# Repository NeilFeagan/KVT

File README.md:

# KVT
Open source southpaw mechanical keyboard. This Github comes with both the project files and libraries used on the project.
Note I do not own the libraries used, I have only modified them to fit my needs.

## Features
* USB Type-C
* Southpaw Layout
* All Through Hole Components
* LED Support
* QMK

## Bill Of Materials
* Proton_C: 1
* KVT PCB: 1
* MX Style Switches: 104
* 1N4148 Through Hole Diodes: 104
* JS202011AQN DPDT Switch: 1 (Right Angle)
* 470Ω resistors: 104
* LEDs: 104

## Installing and Compiling
To install QMK visit QMK's official website https://docs.qmk.fm/#/

**You will need all the sub-modules to compile the firmware**

After installation you need to compile the firmware; To compile the firmware for the Proton_C type this into the terminal

```
 make kv\revt:default
```
## Keymaps
Default Keymap

FN Layer Keymap

## Warning
This keyboard does not include a backplate or case, you will have to make your own.

KiCad 5.1.2 or above is needed to open this project. KiCad 4 or below won't work.

## Notes
I made this keyboard for a personal project, I am new to the circuit/keyboard designing in game. If you open the pcb design you will see a bunch of numbers to the left of the finished design, those are spacing numbers for the footprints that I used.   

If you have any suggestions on improving the design message me on Reddit /u/Hybrid65, thank you.

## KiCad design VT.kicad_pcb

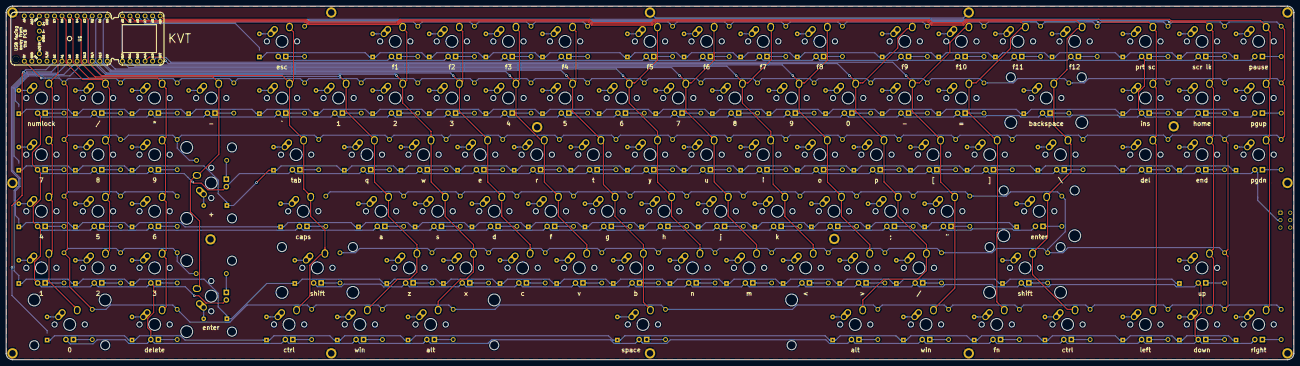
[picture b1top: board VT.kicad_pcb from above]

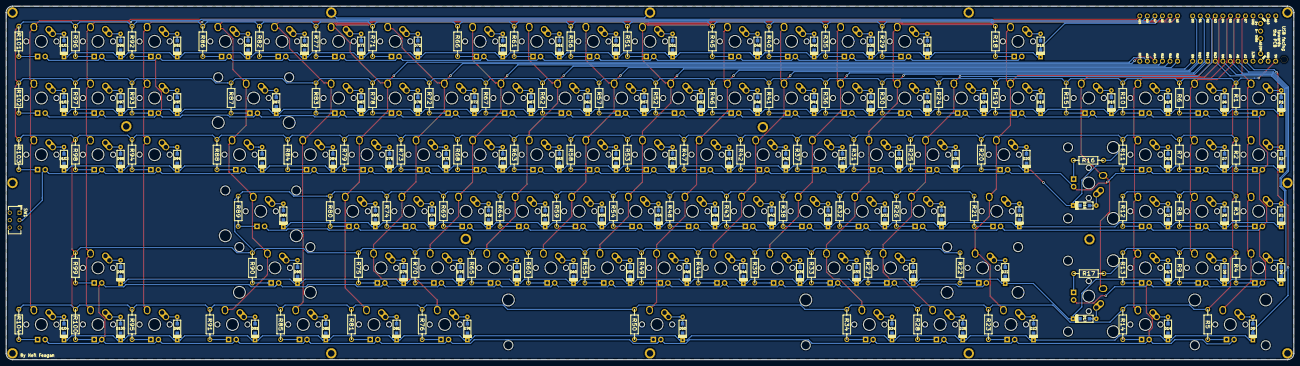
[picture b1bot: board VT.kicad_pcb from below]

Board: 2 copper layers, 433.3 x 119.0 mm, 434 parts (210 on the bottom side), 238 nets.

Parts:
D1, D2, D3, D4, D5, D6, D7, D8, D9, D10, D11, D12, D13, D14, D15, D16, D17, D18, D19, D20, D21, D22, D23, D24, D25, D26, D27, D28, D29, D30, D31, D32, D33, D34, D35, D36, D37, D38, D39, D40, D41, D42, D43, D44, D45, D46, D47, D48, D49, D50, D51, D52, D53, D54, D55, D56, D57, D58, D59, D60, D61, D62, D63, D64, D65, D66, D67, D68, D69, D70, D71, D72, D73, D74, D75, D76, D77, D78, D79, D80, D81, D82, D83, D84, D85, D86, D87, D88, D89, D90, D91, D92, D93, D94, D95, D96, D97, D98, D99, D100, D101, D102, D103, D104: D; D_SOD123_axial
D105, D106, D107, D108, D109, D110, D111, D112, D113, D114, D115, D116, D117, D118, D119, D120, D121, D122, D123, D124, D125, D126, D127, D128, D129, D130, D131, D132, D133, D134, D135, D136, D137, D138, D139, D140, D141, D142, D143, D144, D145, D146, D147, D148, D149, D150, D151, D152, D153, D154, D155, D156, D157, D158, D159, D160, D161, D162, D163, D164, D165, D166, D167, D168, D169, D170, D171, D172, D173, D174, D175, D176, D177, D178, D179, D180, D181, D182, D183, D184, D185, D186, D187, D188, D189, D190, D191, D192, D193, D194, D195, D196, D197, D198, D199, D200, D201, D202, D203, D204, D205, D206, D207, D208: LED; LED_E
H1, H2, H3, H4, H5, H6, H7, H8, H9, H10, H11, H12, H13, H14, H15, H16: MH_Pad; MountingHole_2.2mm_M2_ISO7380_Pad
K1, K2, K3, K4, K6, K7, K8, K9, K10, K11, K12, K13, K14, K15, K18, K19, K24, K25, K26, K27, K29, K30, K31, K32, K33, K35, K36, K37, K38, K39, K40, K41, K42, K43, K44, K45, K46, K47, K48, K49, K51, K52, K53, K54, K55, K56, K57, K58, K59, K60, K61, K62, K63, K64, K65, K66, K67, K68, K69, K70, K71, K72, K73, K74, K75, K77, K78, K79, K80, K82, K83, K84, K86, K92, K93, K94, K95, K96, K97, K98, K99, K100, K101, K102, K103, K104: KEYSW; MX-1U-NoLED_E
K5, K16, K17: KEYSW; MX-2U-ReversedStabilizers-NoLED_E
K20, K88: KEYSW; MX-1.5U-NoLED_E
K21: KEYSW; MX-1.75U-NoLED_E
K22, K89: KEYSW; MX-2.25U-NoLED_E
K23, K28, K34, K76, K81, K85, K91: KEYSW; MX-1.25U-NoLED_E
K50: KEYSW; MX-6.25U-ReversedStabilizers-NoLED_E
K87: KEYSW; MX-2U-NoLED_E
K90: KEYSW; MX-2.75U-NoLED_E
R1, R2, R3, R4, R5, R6, R7, R8, R9, R10, R11, R12, R13, R14, R15, R16, R17, R18, R19, R20, R21, R22, R23, R24, R25, R26, R27, R28, R29, R30, R31, R32, R33, R34, R35, R36, R37, R38, R39, R40, R41, R42, R43, R44, R45, R46, R47, R48, R49, R50, R51, R52, R53, R54, R55, R56, R57, R58, R59, R60, R61, R62, R63, R64, R65, R66, R67, R68, R69, R70, R71, R72, R73, R74, R75, R76, R77, R78, R79, R80, R81, R82, R83, R84, R85, R86, R87, R88, R89, R90, R91, R92, R93, R94, R95, R96, R97, R98, R99, R100, R101, R102, R103, R104: 470; RESISTOR
SW1: SW_SPST; SW_CuK_JS202011AQN_DPDT_Angled
U1: proton_c; proton_c_E

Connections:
/col0: K1.1, K2.1, K3.1, K4.1, K5.1, U1.B7
/col1: K6.1, K7.1, K8.1, K9.1, U1.B6
/col2: K10.1, K11.1, K12.1, K13.1, K14.1, U1.B5
/col3: K15.1, K16.1, K17.1, U1.B4
/col4: K18.1, K19.1, K20.1, K21.1, K22.1, K23.1, U1.B3
/col5: K24.1, K25.1, K26.1, K27.1, K28.1, U1.B2
/col6: K29.1, K30.1, K31.1, K32.1, K33.1, K34.1, U1.B14
/col7: K35.1, K36.1, K37.1, K38.1, K39.1, U1.B1
/col8: K40.1, K41.1, K42.1, K43.1, K44.1, U1.B15
/col9: K45.1, K46.1, K47.1, K48.1, K49.1, K50.1, U1.B0
/col10: K51.1, K52.1, K53.1, K54.1, K55.1, U1.B9
/col11: K56.1, K57.1, K58.1, K59.1, K60.1, U1.B10
/col12: K61.1, K62.1, K63.1, K64.1, K65.1, U1.B11
/col13: K66.1, K67.1, K68.1, K69.1, K70.1, U1.B12
/col14: K71.1, K72.1, K73.1, K74.1, K75.1, K76.1, U1.A14
/col15: K77.1, K78.1, K79.1, K80.1, K81.1, U1.A13
/col16: K82.1, K83.1, K84.1, K85.1, U1.A4
/col17: K86.1, K87.1, K88.1, K89.1, K90.1, K91.1, U1.A5
/col18: K92.1, K93.1, K94.1, K95.1, U1.A7
/col19: K96.1, K97.1, K98.1, K99.1, K100.1, U1.A8
/col20: K101.1, K102.1, K103.1, K104.1, U1.A15
/row0: D18.1, D29.1, D35.1, D40.1, D45.1, D51.1, D56.1, D61.1, D66.1, D71.1, D77.1, D82.1, D86.1, D92.1, D96.1, D101.1, U1.A6
/row1: D1.1, D6.1, D10.1, D15.1, D19.1, D24.1, D30.1, D36.1, D41.1, D46.1, D52.1, D57.1, D62.1, D67.1, D72.1, D78.1, D83.1, D87.1, D93.1, D97.1, D102.1, U1.B13
/row2: D2.1, D7.1, D11.1, D16.1, D20.1, D25.1, D31.1, D37.1, D42.1, D47.1, D53.1, D58.1, D63.1, D68.1, D73.1, D79.1, D84.1, D88.1, D94.1, D98.1, D103.1, U1.B8
/row3: D3.1, D8.1, D12.1, D21.1, D26.1, D32.1, D38.1, D43.1, D48.1, D54.1, D59.1, D64.1, D69.1, D74.1, D80.1, D89.1, U1.A0
/row4: D4.1, D9.1, D13.1, D17.1, D22.1, D27.1, D33.1, D39.1, D44.1, D49.1, D55.1, D60.1, D65.1, D70.1, D75.1, D90.1, D99.1, U1.A1
/row5: D5.1, D14.1, D23.1, D28.1, D34.1, D50.1, D76.1, D81.1, D85.1, D91.1, D95.1, D100.1, D104.1, U1.A2
GND: H1.1, H2.1, H3.1, H4.1, H5.1, H6.1, H7.1, H8.1, H9.1, H10.1, H11.1, H12.1, H13.1, H14.1, H15.1, H16.1, SW1.1, U1.GND
unnamed: D1.2, K1.2
unnamed: D2.2, K2.2
unnamed: D3.2, K3.2
unnamed: D4.2, K4.2
unnamed: D5.2, K5.2
unnamed: D6.2, K6.2
unnamed: D7.2, K7.2
unnamed: D8.2, K8.2
unnamed: D9.2, K9.2
unnamed: D10.2, K10.2
unnamed: D11.2, K11.2
unnamed: D12.2, K12.2
unnamed: D13.2, K13.2
unnamed: D14.2, K14.2
unnamed: D15.2, K15.2
unnamed: D16.2, K16.2
unnamed: D17.2, K17.2
unnamed: D18.2, K18.2
unnamed: D19.2, K19.2
unnamed: D20.2, K20.2
unnamed: D21.2, K21.2
unnamed: D22.2, K22.2
unnamed: D23.2, K23.2
unnamed: D24.2, K24.2
unnamed: D25.2, K25.2
unnamed: D26.2, K26.2
unnamed: D27.2, K27.2
unnamed: D28.2, K28.2
unnamed: D29.2, K29.2
unnamed: D30.2, K30.2
unnamed: D31.2, K31.2
unnamed: D32.2, K32.2
unnamed: D33.2, K33.2
unnamed: D34.2, K34.2
unnamed: D35.2, K35.2
unnamed: D36.2, K36.2
unnamed: D37.2, K37.2
unnamed: D38.2, K38.2
unnamed: D39.2, K39.2
unnamed: D40.2, K40.2
unnamed: D41.2, K41.2
unnamed: D42.2, K42.2
unnamed: D43.2, K43.2
unnamed: D44.2, K44.2
unnamed: D45.2, K45.2
unnamed: D46.2, K46.2
unnamed: D47.2, K47.2
unnamed: D48.2, K48.2
unnamed: D49.2, K49.2
unnamed: D50.2, K50.2
unnamed: D51.2, K51.2
unnamed: D52.2, K52.2
unnamed: D53.2, K53.2
unnamed: D54.2, K54.2
unnamed: D55.2, K55.2
unnamed: D56.2, K56.2
unnamed: D57.2, K57.2
unnamed: D58.2, K58.2
unnamed: D59.2, K59.2
unnamed: D60.2, K60.2
unnamed: D61.2, K61.2
unnamed: D62.2, K62.2
unnamed: D63.2, K63.2
unnamed: D64.2, K64.2
unnamed: D65.2, K65.2
unnamed: D66.2, K66.2
unnamed: D67.2, K67.2
unnamed: D68.2, K68.2
unnamed: D69.2, K69.2
unnamed: D70.2, K70.2
unnamed: D71.2, K71.2
unnamed: D72.2, K72.2
unnamed: D73.2, K73.2
unnamed: D74.2, K74.2
unnamed: D75.2, K75.2
unnamed: D76.2, K76.2
unnamed: D77.2, K77.2
unnamed: D78.2, K78.2
unnamed: D79.2, K79.2
unnamed: D80.2, K80.2
unnamed: D81.2, K81.2
unnamed: D82.2, K82.2
unnamed: D83.2, K83.2
unnamed: D84.2, K84.2
unnamed: D85.2, K85.2
unnamed: D86.2, K86.2
unnamed: D87.2, K87.2
unnamed: D88.2, K88.2
unnamed: D89.2, K89.2
unnamed: D90.2, K90.2
unnamed: D91.2, K91.2
unnamed: D92.2, K92.2
unnamed: D93.2, K93.2
unnamed: D94.2, K94.2
unnamed: D95.2, K95.2
unnamed: D96.2, K96.2
unnamed: D97.2, K97.2
unnamed: D98.2, K98.2
unnamed: D99.2, K99.2
unnamed: D100.2, K100.2
unnamed: D101.2, K101.2
unnamed: D102.2, K102.2
unnamed: D103.2, K103.2
unnamed: D104.2, K104.2
unnamed: D105.1, D106.1, D107.1, D108.1, D109.1, D110.1, D111.1, D112.1, D113.1, D114.1, D115.1, D116.1, D117.1, D118.1, D119.1, D120.1, D121.1, D122.1, D123.1, D124.1, D125.1, D126.1, D127.1, D128.1, D129.1, D130.1, D131.1, D132.1, D133.1, D134.1, D135.1, D136.1, D137.1, D138.1, D139.1, D140.1, D141.1, D142.1, D143.1, D144.1, D145.1, D146.1, D147.1, D148.1, D149.1, D150.1, D151.1, D152.1, D153.1, D154.1, D155.1, D156.1, D157.1, D158.1, D159.1, D160.1, D161.1, D162.1, D163.1, D164.1, D165.1, D166.1, D167.1, D168.1, D169.1, D170.1, D171.1, D172.1, D173.1, D174.1, D175.1, D176.1, D177.1, D178.1, D179.1, D180.1, D181.1, D182.1, D183.1, D184.1, D185.1, D186.1, D187.1, D188.1, D189.1, D190.1, D191.1, D192.1, D193.1, D194.1, D195.1, D196.1, D197.1, D198.1, D199.1, D200.1, D201.1, D202.1, D203.1, D204.1, D205.1, D206.1, D207.1, D208.1, SW1.2
unnamed: D105.2, R1.2
unnamed: D106.2, R2.2
unnamed: D107.2, R3.2
unnamed: D108.2, R4.2
unnamed: D109.2, R5.2
unnamed: D110.2, R6.2
unnamed: D111.2, R7.2
unnamed: D112.2, R8.2
unnamed: D113.2, R9.2
unnamed: D114.2, R10.2
unnamed: D115.2, R11.2
unnamed: D116.2, R12.2
unnamed: D117.2, R13.2
unnamed: D118.2, R14.2
unnamed: D119.2, R15.2
unnamed: D120.2, R16.2
unnamed: D121.2, R17.2
unnamed: D122.2, R18.2
unnamed: D123.2, R19.2
unnamed: D124.2, R20.2
unnamed: D125.2, R21.2
unnamed: D126.2, R22.2
unnamed: D127.2, R23.2
unnamed: D128.2, R24.2
unnamed: D129.2, R25.2
unnamed: D130.2, R26.2
unnamed: D131.2, R27.2
unnamed: D132.2, R28.2
unnamed: D133.2, R29.2
unnamed: D134.2, R30.2
unnamed: D135.2, R31.2
unnamed: D136.2, R32.2
unnamed: D137.2, R33.2
unnamed: D138.2, R34.2
unnamed: D139.2, R35.2
unnamed: D140.2, R36.2
unnamed: D141.2, R37.2
unnamed: D142.2, R38.2
unnamed: D143.2, R39.2
unnamed: D144.2, R40.2
unnamed: D145.2, R41.2
unnamed: D146.2, R42.2
unnamed: D147.2, R43.2
unnamed: D148.2, R44.2
unnamed: D149.2, R45.2
unnamed: D150.2, R46.2
unnamed: D151.2, R47.2
unnamed: D152.2, R48.2
unnamed: D153.2, R49.2
unnamed: D154.2, R50.2
unnamed: D155.2, R51.2
unnamed: D156.2, R52.2
unnamed: D157.2, R53.2
unnamed: D158.2, R54.2
unnamed: D159.2, R55.2
unnamed: D160.2, R56.2
unnamed: D161.2, R57.2
unnamed: D162.2, R58.2
unnamed: D163.2, R59.2
unnamed: D164.2, R60.2
unnamed: D165.2, R61.2
unnamed: D166.2, R62.2
unnamed: D167.2, R63.2
unnamed: D168.2, R64.2
unnamed: D169.2, R65.2
unnamed: D170.2, R66.2
unnamed: D171.2, R67.2
unnamed: D172.2, R68.2
unnamed: D173.2, R69.2
unnamed: D174.2, R70.2
unnamed: D175.2, R71.2
unnamed: D176.2, R72.2
unnamed: D177.2, R73.2
unnamed: D178.2, R74.2
unnamed: D179.2, R75.2
unnamed: D180.2, R76.2
unnamed: D181.2, R77.2
unnamed: D182.2, R78.2
unnamed: D183.2, R79.2
unnamed: D184.2, R80.2
unnamed: D185.2, R81.2
unnamed: D186.2, R82.2
unnamed: D187.2, R83.2
unnamed: D188.2, R84.2
unnamed: D189.2, R85.2
unnamed: D190.2, R86.2
unnamed: D191.2, R87.2
unnamed: D192.2, R88.2
unnamed: D193.2, R89.2
unnamed: D194.2, R90.2
unnamed: D195.2, R91.2
unnamed: D196.2, R92.2
unnamed: D197.2, R93.2
unnamed: D198.2, R94.2
unnamed: D199.2, R95.2
unnamed: D200.2, R96.2
unnamed: D201.2, R97.2
unnamed: D202.2, R98.2
unnamed: D203.2, R99.2
unnamed: D204.2, R100.2
unnamed: D205.2, R101.2
unnamed: D206.2, R102.2
unnamed: D207.2, R103.2
unnamed: D208.2, R104.2
VCC: R1.1, R2.1, R3.1, R4.1, R5.1, R6.1, R7.1, R8.1, R9.1, R10.1, R11.1, R12.1, R13.1, R14.1, R15.1, R16.1, R17.1, R18.1, R19.1, R20.1, R21.1, R22.1, R23.1, R24.1, R25.1, R26.1, R27.1, R28.1, R29.1, R30.1, R31.1, R32.1, R33.1, R34.1, R35.1, R36.1, R37.1, R38.1, R39.1, R40.1, R41.1, R42.1, R43.1, R44.1, R45.1, R46.1, R47.1, R48.1, R49.1, R50.1, R51.1, R52.1, R53.1, R54.1, R55.1, R56.1, R57.1, R58.1, R59.1, R60.1, R61.1, R62.1, R63.1, R64.1, R65.1, R66.1, R67.1, R68.1, R69.1, R70.1, R71.1, R72.1, R73.1, R74.1, R75.1, R76.1, R77.1, R78.1, R79.1, R80.1, R81.1, R82.1, R83.1, R84.1, R85.1, R86.1, R87.1, R88.1, R89.1, R90.1, R91.1, R92.1, R93.1, R94.1, R95.1, R96.1, R97.1, R98.1, R99.1, R100.1, R101.1, R102.1, R103.1, R104.1, U1.5V

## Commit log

2020-01-12 Master
2020-01-14 Images
2020-01-28 Fixed Issues
